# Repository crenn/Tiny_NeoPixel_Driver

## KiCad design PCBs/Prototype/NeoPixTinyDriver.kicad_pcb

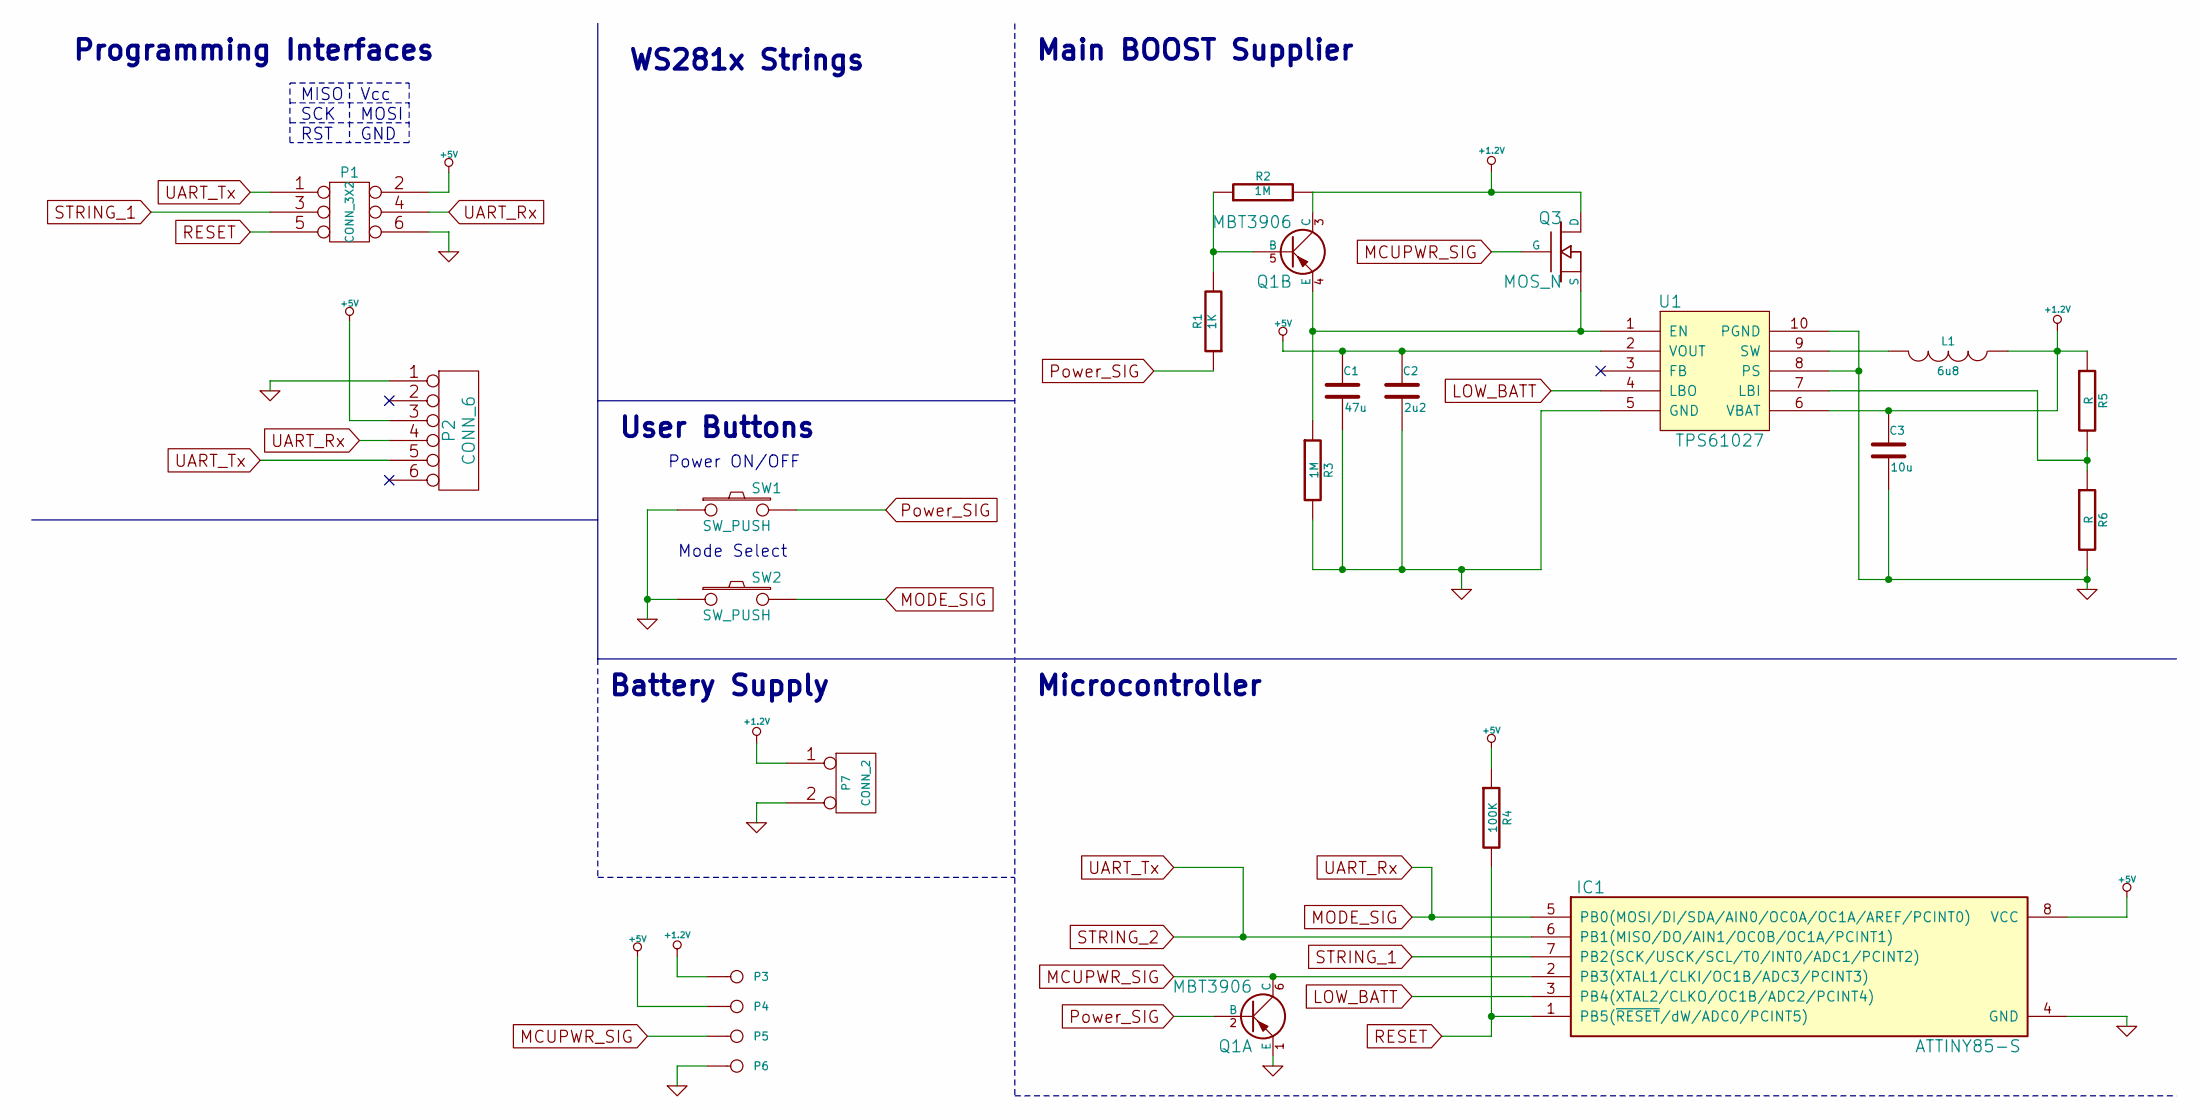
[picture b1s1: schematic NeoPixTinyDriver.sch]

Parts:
C1: 47u
C2: 2u2
C3: 10u
IC1: ATTINY85-S; SO8-200
L1: 6u8
P1: CONN_3X2
P2: CONN_6
P3, P4, P5, P6: CONN_1
P7: CONN_2
Q1: MBT3906
Q3: MOS_N
R1: 1K
R2, R3: 1M
R4: 100K
R5, R6: R
SW1, SW2: SW_PUSH
U1: TPS61027

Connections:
+1.2V: C3.1, L1.1, P3.1, P7.1, Q1.3 (C), Q3.3 (D), R2.2, R5.1, U1.6 (VBAT)
+5V: C1.1, C2.1, IC1.8 (VCC), P1.2, P2.3, P4.1, R4.1, U1.2 (VOUT)
GND: C1.2, C2.2, C3.2, IC1.4 (GND), P1.6, P2.1, P6.1, P7.2 (PM), Q1.1 (E), R3.2, R6.2, SW1.1, SW2.1, U1.5 (GND), U1.8 (PS), U1.10 (PGND)
LOW_BATT: IC1.3 (PB4(XTAL2/CLKO/OC1B/ADC2/PCINT4)), U1.4 (LBO)
MCUPWR_SIG: IC1.2 (PB3(XTAL1/CLKI/OC1B/ADC3/PCINT3)), P5.1, Q1.6 (C), Q3.1 (G)
MODE_SIG: IC1.5 (PB0(MOSI/DI/SDA/AIN0/OC0A/OC1A/AREF/PCI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), P1.4, P2.4, SW2.2
unnamed: Q1.5 (B), R1.2, R2.1
unnamed: Q1.4 (E), Q3.2 (S), R3.1, U1.1 (EN)
unnamed: R5.2, R6.1, U1.7 (LBI)
unnamed: L1.2, U1.9 (SW)
Power_SIG: Q1.2 (B), R1.1, SW1.2
RESET: IC1.1 (PB5(~RESET~/dW/ADC0/PCINT5)), P1.5, R4.2
STRING_1: IC1.7 (PB2(SCK/USCK/SCL/T0/INT0/ADC1/PCINT2)), P1.3
STRING_2: IC1.6 (PB1(MISO/DO/AIN1/OC0B/OC1A/PCINT1)), P1.1, P2.5

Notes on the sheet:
Power ON/OFF
Mode Select
Vcc
MOSI
GND
RST
SCK
MISO
Programming Interfaces
WS281x Strings
User Buttons
Main BOOST Supplier
Microcontroller
Battery Supply

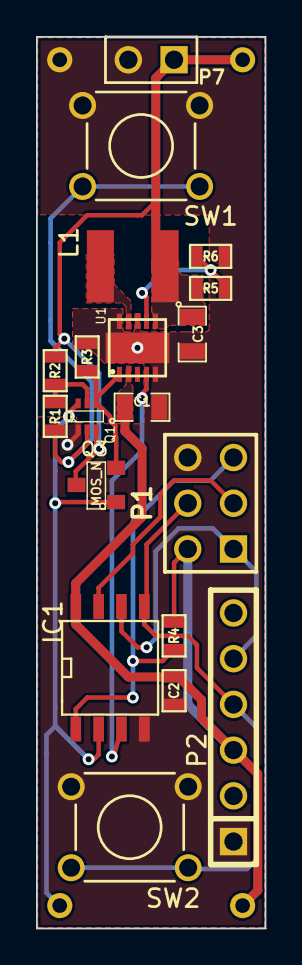
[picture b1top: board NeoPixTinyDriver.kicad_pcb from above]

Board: 2 copper layers, 12.7 x 49.5 mm, 23 parts (0 on the bottom side), 14 nets.

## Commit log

2014-08-15 Initial Commit
    Add license file and PCB files for the current prototype
2014-08-15 Add in a simple demo program
    Flash each colour of the 8 Neopixels then cycle rainbow colours on all
    pixels.
2014-08-15 Code cleanup and minor bug fix
    Wheel function wasn't doing calculations in correct order.
2014-08-16 Add in handling to turn off device
    Debounce the power button, and pull the pin low after a short period.

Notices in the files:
PCBs/Prototype/NeoPixTinyDriver.kicad_pcb:
CC BY-SA v3.0
